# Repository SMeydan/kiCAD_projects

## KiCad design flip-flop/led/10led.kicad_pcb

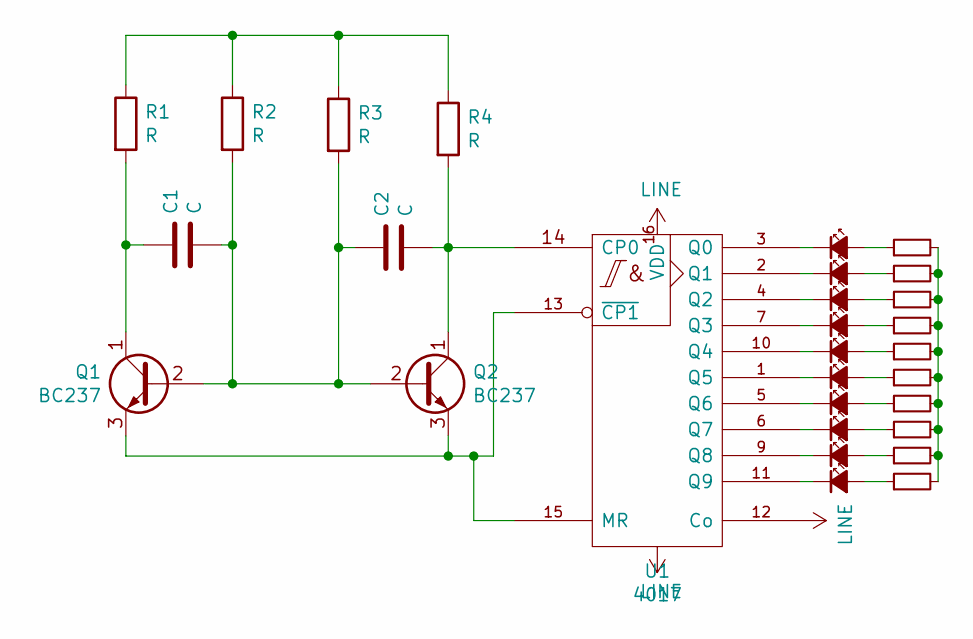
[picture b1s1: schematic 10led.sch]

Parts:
C1, C2: C; C_Axial_L3.8mm_D2.6mm_P7.50mm_Horizontal
D1, D2, D3, D4, D5, D6, D7, D8, D9, D10: LED_Small_ALT; LED_D3.0mm
Q1, Q2: BC237; TO-92_Inline
R1, R2, R3, R4: R; R_Axial_DIN0204_L3.6mm_D1.6mm_P5.08mm_Horizontal
R5, R6, R7, R8, R9, R10, R11, R12, R13, R14: R_Small; R_Axial_DIN0204_L3.6mm_D1.6mm_P5.08mm_Horizontal
U1: 4017

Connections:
LINE: U1.8 (VSS), U1.12 (Co), U1.16 (VDD)
unnamed: C1.1, Q1.1 (C), R1.2
unnamed: C1.2, C2.1, Q1.2 (B), Q2.2 (B), R2.2, R3.2
unnamed: C2.2, Q2.1 (C), R4.2, U1.14 (CP0)
unnamed: D1.1 (K), U1.3 (Q0)
unnamed: D1.2 (A), R5.1
unnamed: D2.1 (K), U1.2 (Q1)
unnamed: D2.2 (A), R6.1
unnamed: D3.1 (K), U1.4 (Q2)
unnamed: D3.2 (A), R7.1
unnamed: D4.1 (K), U1.7 (Q3)
unnamed: D4.2 (A), R8.1
unnamed: D5.1 (K), U1.10 (Q4)
unnamed: D5.2 (A), R9.1
unnamed: D6.1 (K), U1.1 (Q5)
unnamed: D6.2 (A), R10.1
unnamed: D7.1 (K), U1.5 (Q6)
unnamed: D7.2 (A), R11.1
unnamed: D8.1 (K), U1.6 (Q7)
unnamed: D8.2 (A), R12.1
unnamed: D9.1 (K), U1.9 (Q8)
unnamed: D9.2 (A), R13.1
unnamed: D10.1 (K), U1.11 (Q9)
unnamed: D10.2 (A), R14.1
unnamed: Q1.3 (E), Q2.3 (E), U1.13 (~CP1), U1.15 (MR)
unnamed: R1.1, R2.1, R3.1, R4.1
unnamed: R5.2, R6.2, R7.2, R8.2, R9.2, R10.2, R11.2, R12.2, R13.2, R14.2

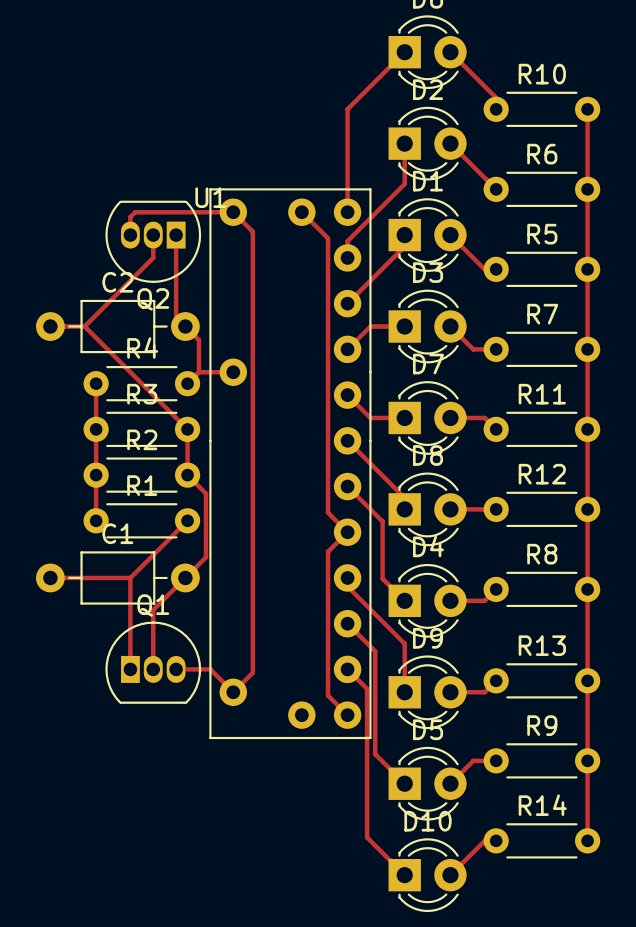
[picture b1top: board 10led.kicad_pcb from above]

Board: 2 copper layers, 29 parts (0 on the bottom side), 27 nets.

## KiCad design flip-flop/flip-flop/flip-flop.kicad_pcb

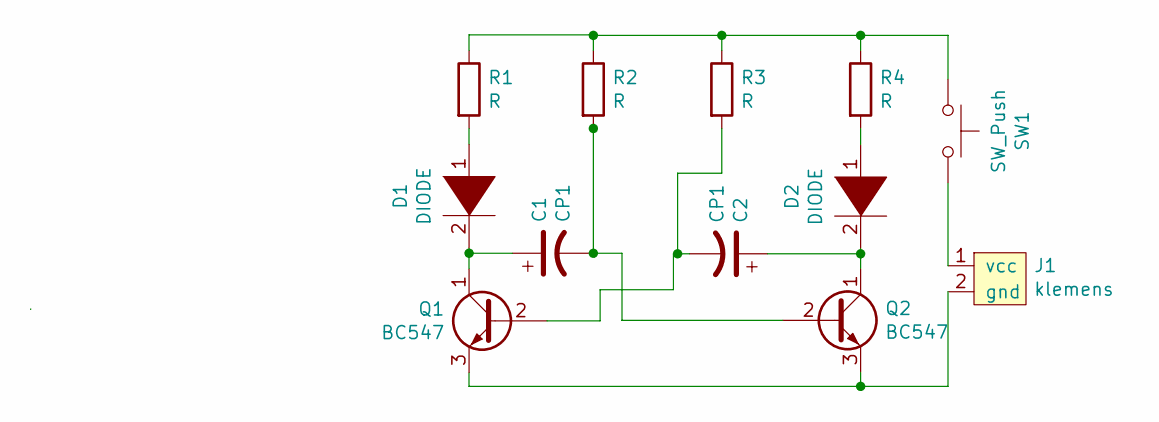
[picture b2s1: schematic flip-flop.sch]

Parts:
C1, C2: CP1; CP_Radial_D4.0mm_P1.50mm
D1, D2: DIODE; LED_D3.0mm
J1: klemens
Q1, Q2: BC547; TO-92_Inline
R1, R2, R3, R4: R; R_Axial_DIN0411_L9.9mm_D3.6mm_P20.32mm_Horizontal
SW1: SW_Push; Panasonic_EVQPUJ_EVQPUA

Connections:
unnamed: C1.1, D1.2 (A), Q1.1 (C)
unnamed: C1.2, Q2.2 (B), R2.2
unnamed: C2.1, D2.2 (A), Q2.1 (C)
unnamed: C2.2, Q1.2 (B), R3.2
unnamed: D1.1 (K), R1.2
unnamed: D2.1 (K), R4.2
unnamed: J1.1 (vcc), SW1.1
unnamed: J1.2 (gnd), Q1.3 (E), Q2.3 (E)
unnamed: R1.1, R2.1, R3.1, R4.1, SW1.2

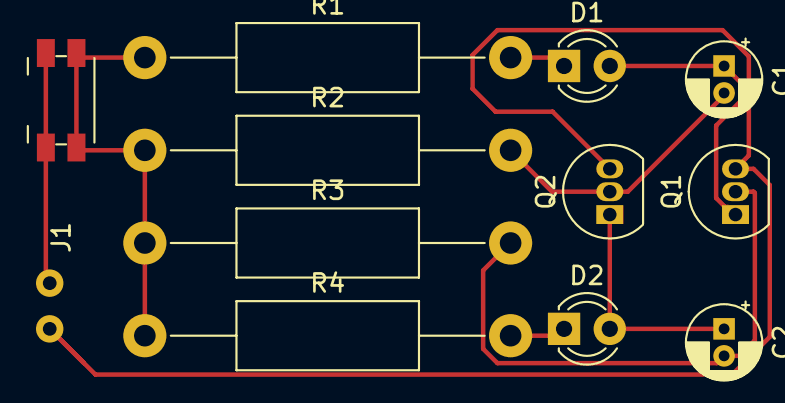
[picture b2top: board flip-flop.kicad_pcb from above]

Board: 2 copper layers, 12 parts (0 on the bottom side), 9 nets.
